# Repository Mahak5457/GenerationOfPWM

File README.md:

# GenerationOfPWM

Link for Tinkercad Simulation for testing of the generated PWM signals:
https://www.tinkercad.com/things/f5y2gFIMZtZ-incredible-krunk/editel?tenant=circuits

About the simulation: The generated PWM signals are tested by connecting the motor to L293D motor driver and connecting the motor driver further to arduino for input signals.

The link for designed pcb is: https://drive.google.com/file/d/1Rq4ow5anfuewHv7m_84eH1Bk5o7s7Xk1/view?usp=sharing

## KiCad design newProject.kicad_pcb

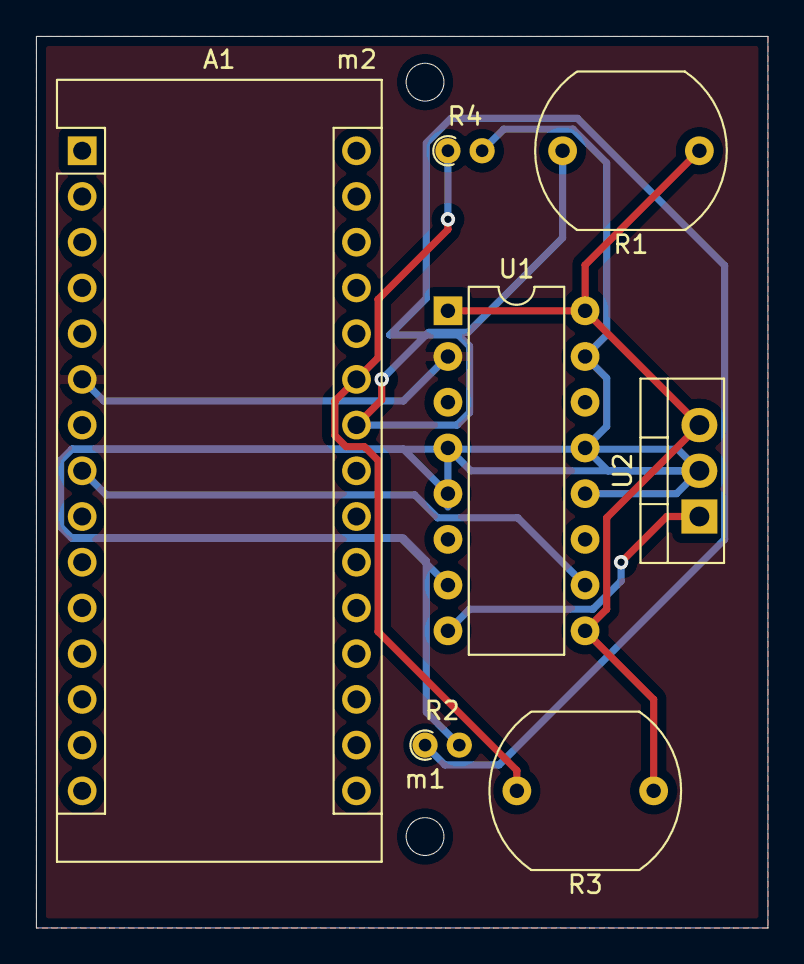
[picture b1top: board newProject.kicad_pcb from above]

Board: 2 copper layers, 40.6 x 49.5 mm, 9 parts (0 on the bottom side), 7 nets.

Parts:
A1: Arduino_Nano_v2.x; Arduino_Nano
R1, R3: LDR03; R_LDR_10x8.5mm_P7.6mm_Vertical
R2, R4: R; R_Axial_DIN0204_L3.6mm_D1.6mm_P1.90mm_Vertical
U1: L293D; DIP-16_W7.62mm
U2: LM7805_TO220; TO-220-3_Vertical
m1, m2: MountingHole_2.1mm

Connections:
+12V: U1.8, U2.1
GND: R2.2, R4.2, U1.4, U1.5, U1.7, U1.12, U1.13, U1.15, U2.2
unnamed: A1.6, U1.2
unnamed: A1.8, U1.10
unnamed: A1.24, R1.2, R2.1
unnamed: A1.25, R3.2, R4.1
unnamed: R1.1, R3.1, U1.1, U1.9, U1.16, U2.3

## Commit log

2021-10-24 Create CodeForPwmGeneration
